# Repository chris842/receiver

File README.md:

# SDR Project
* Software-defined radio receiver, Engineering Electronics ii, Spring 2020
* Partners: Chrisner Garcesa and Andrew Nascimento

## Goal
The goal of this project was to design the schematic for a radio receiver and implement it on a PCB.

## Specifications
The specific goals to achieve given by our professor were as follows:  
* Minimum discernible signal of less than 1uV  
* Image rejection of over 48kHz of band greater than 30dB  
* Tunable range of frequencies greater than 48kHz  
* Band frequency greater than 540kHz  
* Spurious signals below 10uV  

Additional equipment we would have at our disposal would be the Arduino Nano Every

## Block Diagram
  
This is the general design we would follow in order to have a simple, working receiver. It would be our choice on how to implement each element of this design, however we often chose solutions that the professor suggested or other classmates were using as well, but adapted to our needs.

## Schematic
Here is a breakdown of our schematic:

### Bandpass-filter
  
This part of the schematic is to filter our choice of frequencies to capture. We chose a range of 5-10MHz to listen to, so the incoming frequency is filtered through a 2nd order Butterworth filter. The transformer at the end sets the DC operating point of the incoming signal at 2.15V.

### Mixer
  
[This mixer was designed by Dan Tayloe]
(https://www.google.com/url?sa=t&rct=j&q=&esrc=s&source=web&cd=&cad=rja&uact=8&ved=2ahUKEwjM6-jRtvjpAhXiQzABHfqkA9wQFjAAegQIARAB&url=http%3A%2F%2Fwww.norcalqrp.org%2Ffiles%2FTayloe_mixer_x3a.pdf&usg=AOvVaw3V9iSmiFxa8wcdVf5OEluL)

It is simple to implement, is low noise, and allows the bandwidth to be adjusted. The first part of this circuit, the multiplexer, breaks the incoming signal into four outputs, at 0˚, 90˚, 180˚, and 270˚. Then the op-amp, shown below, inverts the redundant sections of the wave and diffferentiates them with their same-phase pair, then outputs two signals, which he calls the In-Phase and Quadrature signals. The op-amp filters the output to the audio-frequency range of up to 25kHz.  

### Clock Generator and Johnson Counter
  
The purpose of this circuit is to drive the multiplexer used in the Tayloe Mixer. The Johnson Counter arrangement of the flip-flops is used to activate the multiplexer switches, selecting the portion of the incoming wave to be inverted and differentiated. The switching frequency is set by an Arduino program.

### Voltage Smoother

Dr. Frohne designed this section of the schematic to provide a stable, ripple-free voltage source. It takes 5 volts from the Arduino and powers the multiplexer, op amp, and DC bias circuit.

### Complete Schematic

## PCB
### Board Schematic
  
PCB design in KiCAD

### Board Render

### Assembled Board

## Tests & Results
### Bandpass Filter
  
The bandpass filter seems to work as expected. There is attenuation up to around 5MHz, where our band begins. A 500mV test signal was used.

### Transformer
  
Our initial winding configuration seemed to only produce noise. An updated winding configuration is shown further below.

### Tayloe Mixer
  
This is not the expected output of the Tayloe mixer. We expected to  a quadrant of a sine wave on each output. Since we cannot verify if the oscillator circuit is working properly, this error may be due to the oscillator.

### Op Amp
  
The op amp seems to be functioning. We can only verify if it works as intended when the Tayloe mixer is working.

### Arduino & Oscillator

Arduino 5V and 3V3 signals appear as expected. Gauging by the serial output, the SDR program seems to be working, but we were not able to capture a signal on the SDA and SCL ports.

## Problems & Things to Fix
### Transformer
We tried a different configuration for the transformer, by winding 18 turns on the primary and 18 on the secondary, and placing a center tap from the 2.15V pad to the middle point of the transformer. We were able to capture a clean sine wave at the transformer input, but not the output. 

### Voltage Divider
We were able trace the 4.3V signal up to where it meets R1 at the voltage divider, but we did not see any voltage across R1 or R2. This can explain why the transformer secondary is not working.

### Tayloe Mixer
The Tayloe mixer is likely not working due to the transformer issue. Since 4.3V is being produced, the output is likely due to the lack of signal reaching the mixer.

### Oscillator
We assume the issue with the oscillator is due to the Arduino program, although it seems to be working fine. It may also be due to improperly placing the surface mount IC on the board. 

## Lessons Learned
### PCB Design
We learned how to design a PCB from start to finish using KiCAD.

### Test Points
Having more test points would make debugging the circuit much easier. We did not include enough test points on the board so it was difficult to get measurements in certain places, and that made it harder to narrow down where issues were originating.

### Trial & Error
While it is important to simulate as much as possible so that a working design is achieved when the board is printed, some things were only able to be debugged when we put the circuit together. Simulation also doesn't account for our personal errors and mishaps, so having extra parts for a future project is important in case we damage parts.

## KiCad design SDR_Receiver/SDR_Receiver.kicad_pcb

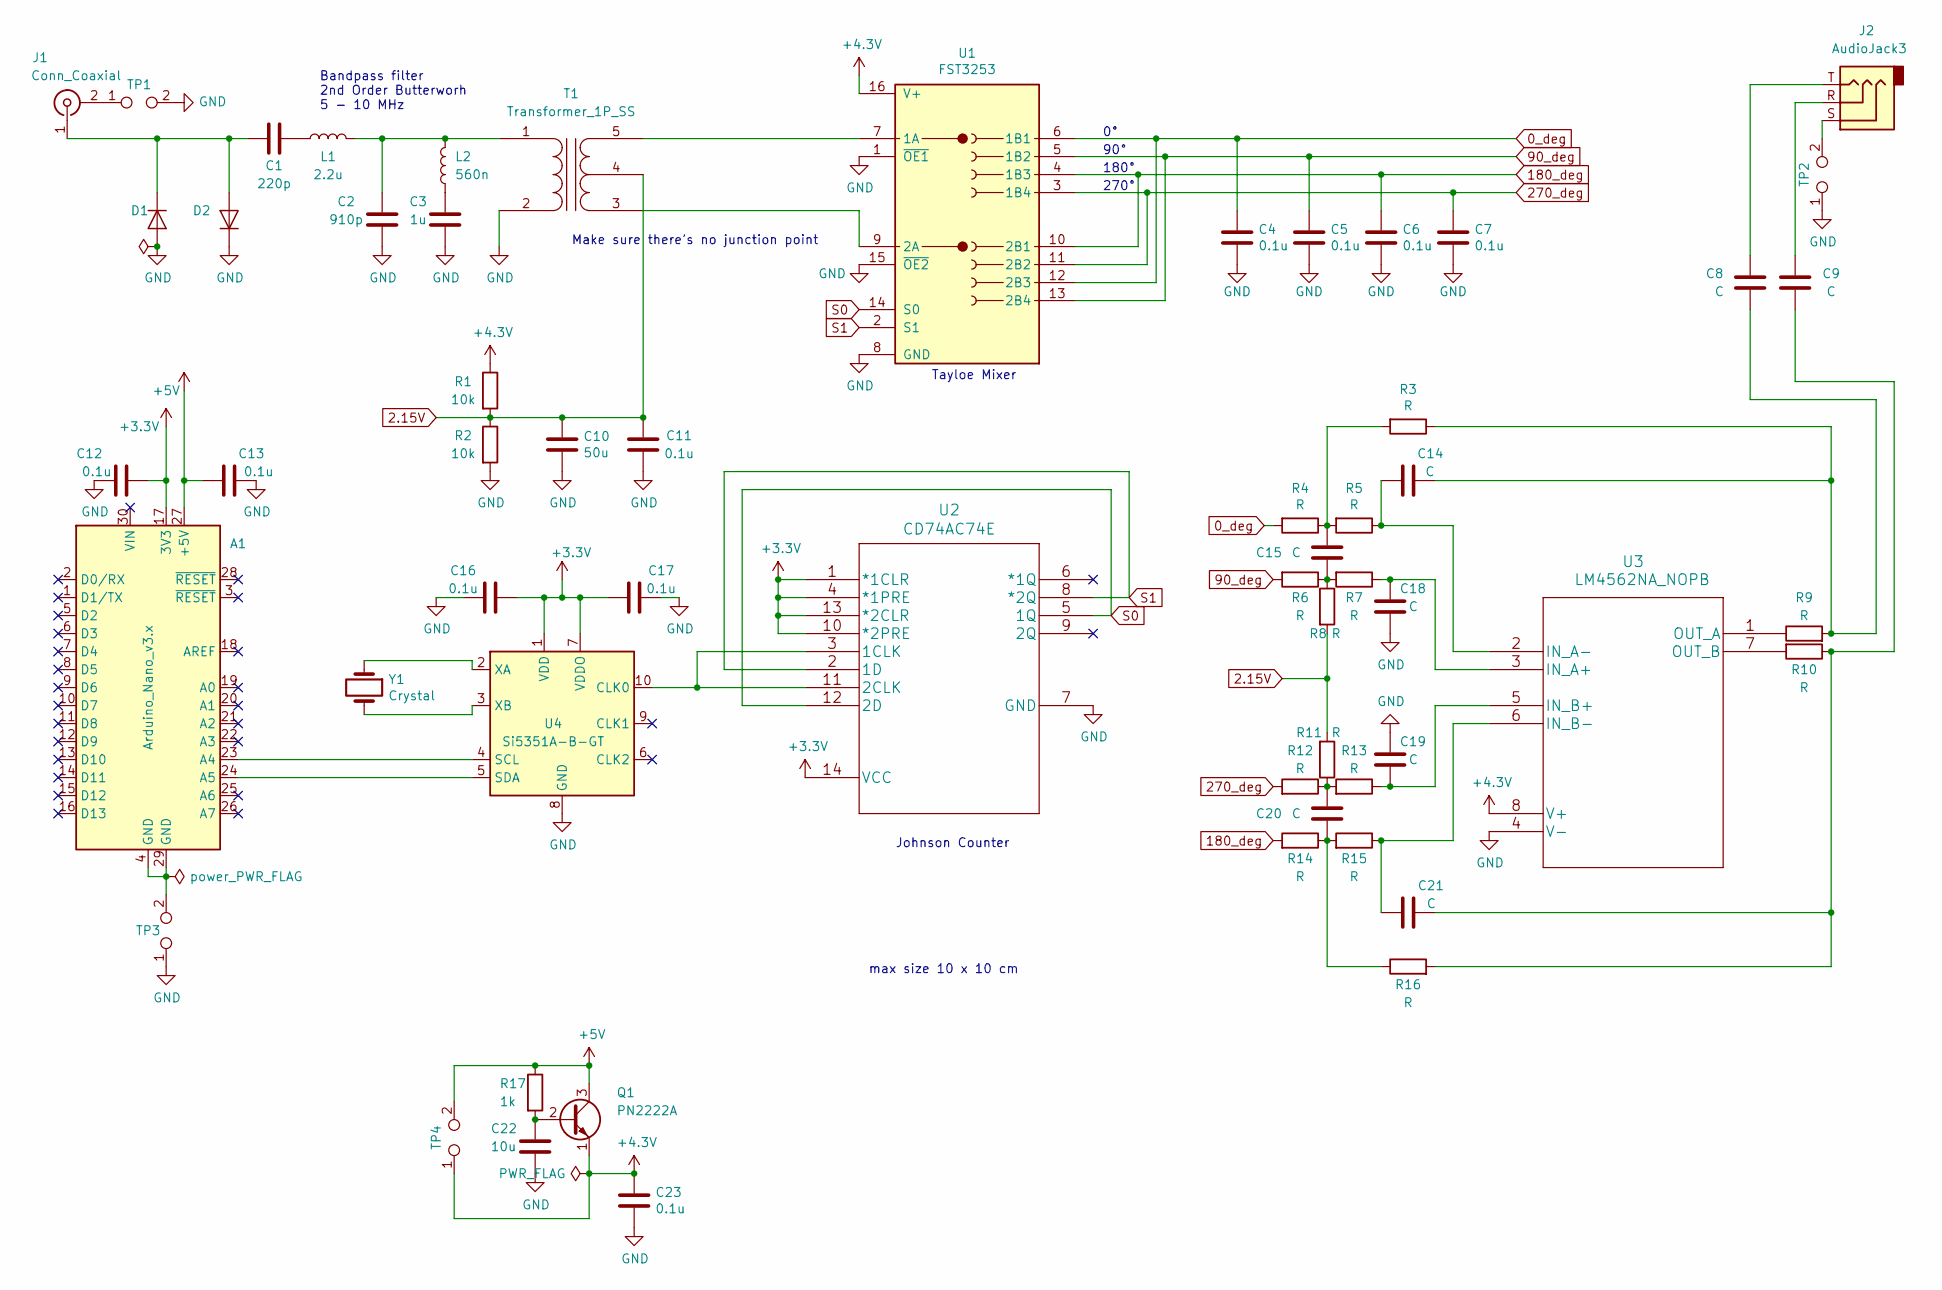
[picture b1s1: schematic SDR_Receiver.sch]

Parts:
A1: Arduino_Nano_v3.x; Arduino_Nano
C1: 220p; CP_Radial_D4.0mm_P1.50mm
C2: 910p; CP_Radial_D4.0mm_P1.50mm
C3: 1u; CP_Radial_D4.0mm_P1.50mm
C4, C5, C6, C7, C11, C12, C13, C16, C17, C23: 0.1u; CP_Radial_D4.0mm_P1.50mm
C8, C9, C14, C15, C18, C19, C20, C21: C; CP_Radial_D4.0mm_P1.50mm
C10: 50u; CP_Radial_D4.0mm_P1.50mm
C22: 10u; CP_Radial_D4.0mm_P1.50mm
D1, D2: D; D_A-405_P7.62mm_Horizontal
J1: Conn_Coaxial; SMA_Samtec_SMA-J-P-X-ST-EM1_EdgeMount
J2: AudioJack3; Jack_3.5mm_Switronic_ST-005-G_horizontal
L1: 2.2u; L_Toroid_Vertical_L10.0mm_W5.0mm_P5.08mm
L2: 560n; L_Toroid_Vertical_L10.0mm_W5.0mm_P5.08mm
Q1: PN2222A; TO-92_Inline
R1, R2: 10k; R_Axial_DIN0207_L6.3mm_D2.5mm_P7.62mm_Horizontal
R3, R4, R5, R6, R7, R8, R9, R10, R11, R12, R13, R14, R15, R16: R; R_Axial_DIN0207_L6.3mm_D2.5mm_P7.62mm_Horizontal
R17: 1k; R_Axial_DIN0207_L6.3mm_D2.5mm_P7.62mm_Horizontal
T1: Transformer_1P_SS; Transformer_Toroid_Tapped_Horizontal_D10.5mm_Amidon-T37
TP1, TP2, TP3, TP4: TestPoint_2Pole; TestPoint_Bridge_Pitch2.54mm_Drill0.7mm
U1: FST3253; SOP65P640X110-16N
U2: CD74AC74E; DIP794W53P254L1930H508Q14N
U3: LM4562NA_NOPB; DIP794W53P254L959H508Q8N
U4: Si5351A-B-GT; MSOP-10_3x3mm_P0.5mm
Y1: Crystal; Crystal_HC49-4H_Vertical

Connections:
0_deg: C4.1, R4.2, U1.6 (1B1), U1.12 (2B3)
2.15V: C10.1, C11.2, R1.2, R2.1, R8.2, R11.2, T1.4 (SC)
90_deg: C5.1, R6.2, U1.5 (1B2), U1.13 (2B4)
180_deg: C6.1, R14.2, U1.4 (1B3), U1.10 (2B1)
270_deg: C7.1, R12.2, U1.3 (1B4), U1.11 (2B2)
+3V3: A1.17 (3V3), C12.2, C16.2, C17.1, U2.1 (*1CLR), U2.4 (*1PRE), U2.10 (*2PRE), U2.13 (*2CLR), U2.14 (VCC), U4.1 (VDD), U4.7 (VDDO)
+4V: C23.1, Q1.1 (E), R1.1, TP4.1, U1.16 (V+), U3.8 (V+)
+5V: A1.27 (+5V), C13.1, Q1.3 (C), R17.1, TP4.2
unnamed: A1.23 (A4), U4.4 (SCL)
unnamed: A1.24 (A5), U4.5 (SDA)
unnamed: A1.4 (GND), A1.29 (GND), TP3.2
unnamed: C1.1, L1.1
unnamed: C1.2, D1.1 (K), D2.2 (A), J1.1 (In)
unnamed: C2.1, L1.2, L2.1, T1.1 (AA)
unnamed: C3.1, L2.2
unnamed: C8.2, J2.T
unnamed: C9.2, J2.R
unnamed: C14.1, R5.1, U3.2 (IN_A-)
unnamed: C8.1, C14.2, R3.1, R9.2
unnamed: C15.1, R3.2, R4.1, R5.2
unnamed: C15.2, R6.1, R7.2, R8.1
unnamed: C18.1, R7.1, U3.3 (IN_A+)
unnamed: C19.1, R13.1, U3.5 (IN_B+)
unnamed: C20.1, R14.1, R15.2, R16.1
unnamed: C20.2, R11.1, R12.1, R13.2
unnamed: C9.1, C21.1, R10.1, R16.2
unnamed: C21.2, R15.1, U3.6 (IN_B-)
unnamed: C22.1, Q1.2 (B), R17.2
unnamed: J1.2 (Ext), TP1.1
unnamed: J2.S, TP2.2
unnamed: R9.1, U3.1 (OUT_A)
unnamed: R10.2, U3.7 (OUT_B)
unnamed: T1.3 (SA), U1.9 (2A)
unnamed: T1.5 (SB), U1.7 (1A)
unnamed: U2.3 (1CLK), U2.11 (2CLK), U4.10 (CLK0)
unnamed: U4.2 (XA), Y1.1
unnamed: U4.3 (XB), Y1.2
S0: U1.14 (S0), U2.5 (1Q), U2.12 (2D)
S1: U1.2 (S1), U2.2 (1D), U2.8 (*2Q)

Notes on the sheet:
Bandpass filter 2nd Order Butterworh 5 - 10 MHz
270°
180°
90°
Tayloe Mixer
Johnson Counter
Make sure there’s no junction point
max size 10 x 10 cm

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
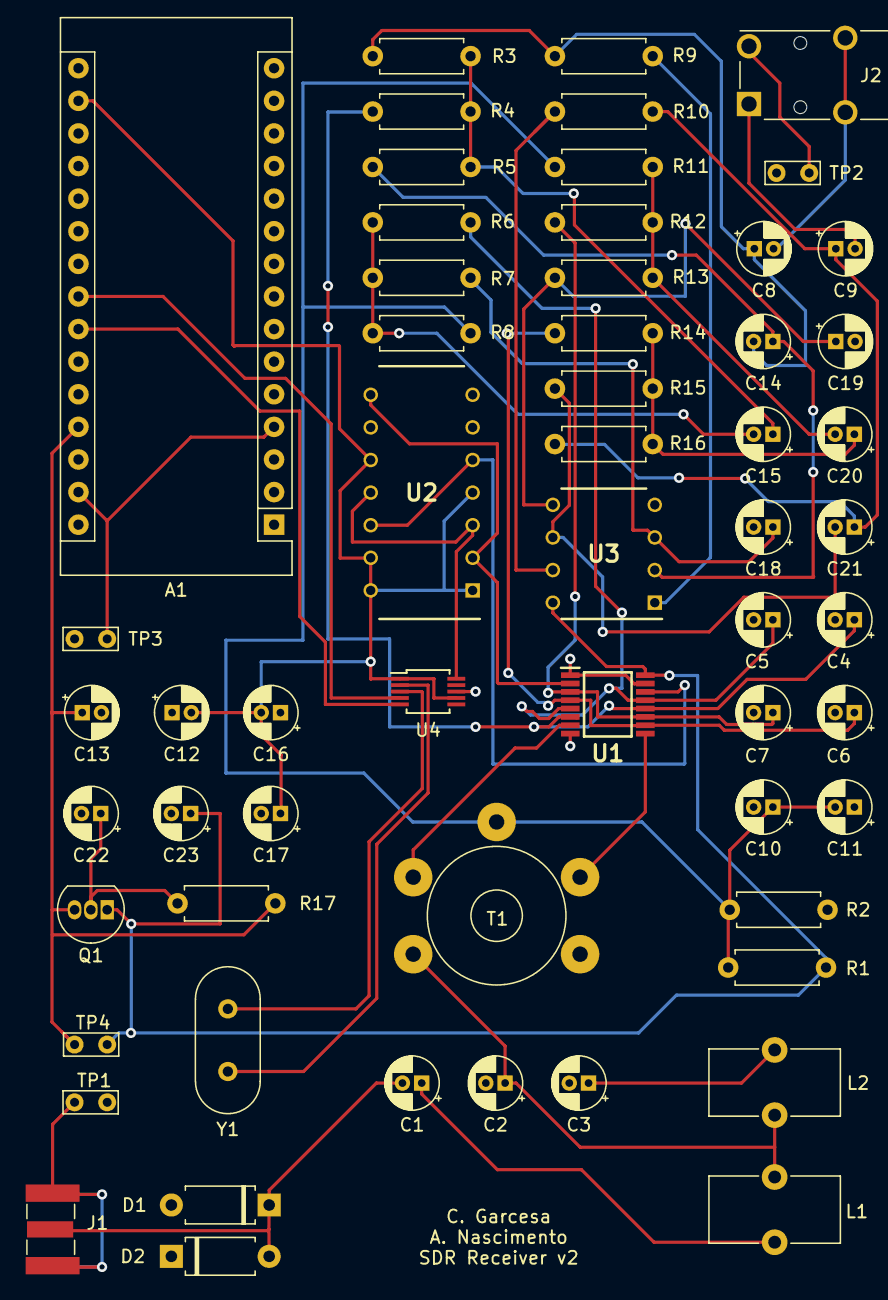
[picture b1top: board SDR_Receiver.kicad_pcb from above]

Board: 2 copper layers, 58 parts (0 on the bottom side), 40 nets.
